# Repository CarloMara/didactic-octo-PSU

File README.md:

# **Didactic PSU**

**An efficient finals project**

So, @nicogela and I decided to build a LAB PSU, but because we're lazy people and we don't like to carry weight we're tring to unite the high efficiency of the switching topologies to the high stability and low noise of the linear ones.

Up until now we've designed the linear stage, and we added to it some DACs in oreder to controll it with a uC. The next stage in the design process will be the testing of the linear + the dacs. If everithing works we will go ahead adding to the desing the switching stage.

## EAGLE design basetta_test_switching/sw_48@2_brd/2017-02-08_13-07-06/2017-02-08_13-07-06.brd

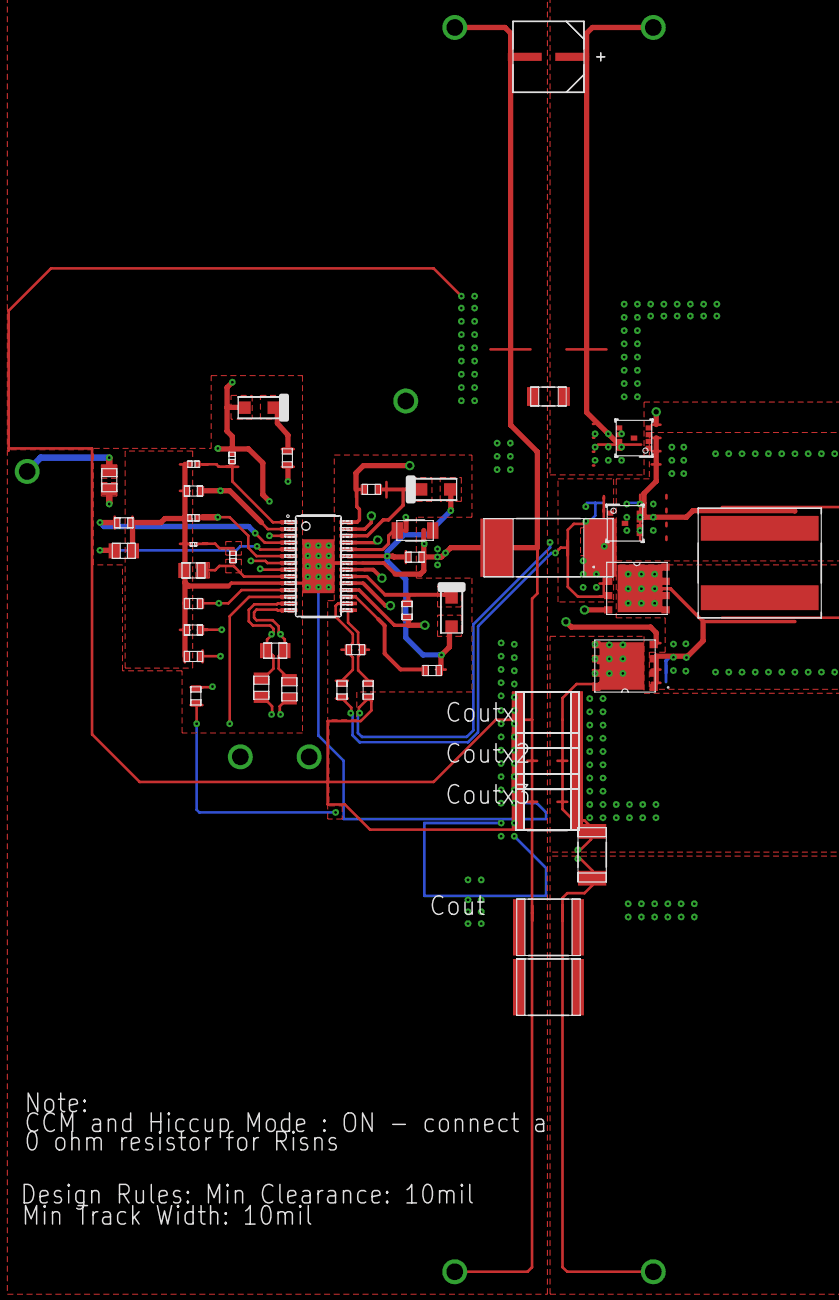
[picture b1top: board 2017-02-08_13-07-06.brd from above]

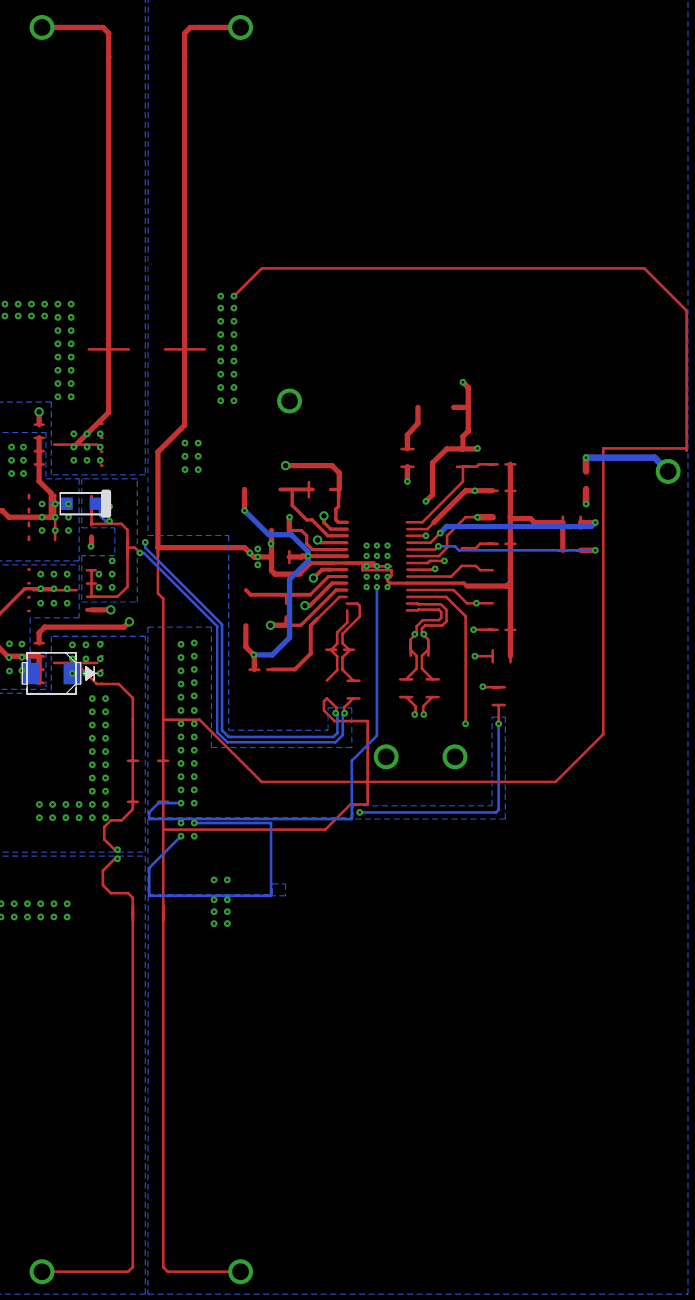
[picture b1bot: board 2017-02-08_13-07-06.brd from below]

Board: 4 copper layers, 66 parts (2 on the bottom side), 27 nets.

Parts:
Cbias: 1206
Cboot1, Cboot2: 0603
Cbulk: SM_RADIAL_6.3AMM
Ccomp: 0201
Ccomp2: 0805
Ccs: 0603
Cdith: 0805
Cf: 0603
Cin: 1206_190
Cisns: 0805
Cout_1, Cout_2: 2220_280
Coutx2_1, Coutx2_2, Coutx2_3, Coutx2_4, Coutx2_5, Coutx3_1, Coutx3_2, Coutx3_3, Coutx3_4, Coutx3_5: 2220
Coutx_1, Coutx_2, Coutx_3, Coutx_4, Coutx_5: 2220
Cslope: 0603
Css: 0603
Csync: 0805
Cvcc: 0603
D2: SOD-123F
D3: SMB
Dboot1, Dboot2: SOD-123F
Df: SOD-123F
GND, GND1: TP-1502
INSNS+: TP-1502
INSNS-: TP-1502
L1: XAL1010
M1, M2: DQG0008A
M3, M4: TRANS_NexFET_Q5A
Rcomp: 0402
Rcsg: 0603
Rcsp: 0603
Rf: 0603
Rfbb: 0603
Rfbt: 0603
Risns: 2512
Risnsn: 0805
Risnsp: 0805
Rmode: 0603
Rpg: 0603
Rsense: 4527
Rt: 0402
Ruvb: 0402
Ruvt: 0402
U1: PWP0028F_N
V1: TP-1502
VIN: TP-1502
VOUT: TP-1502
Vsync: TP-1502

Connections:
0: Cbias.2, Cbulk.2, Ccomp.2, Ccomp2.2, Cdith.1, Cdith.2, Cf.2, Cin.2, Cisns.1, Cisns.2, Cout_1.2, Cout_2.2, Coutx2_1.2, Coutx2_2.2, Coutx2_3.2, Coutx2_4.2, Coutx2_5.2, Coutx3_1.2, Coutx3_2.2, Coutx3_3.2, Coutx3_4.2, Coutx3_5.2, Coutx_1.2, Coutx_2.2, Coutx_3.2, Coutx_4.2, Coutx_5.2, Cslope.2, Css.2, Cvcc.2, GND.1, GND1.1, INSNS+.1, INSNS-.1, Rcsg.2, Rfbb.2, Risnsn.1, Risnsp.1, Rmode.2, Rsense.2, Rt.2, Ruvb.2, U1.5, U1.10, U1.13, U1.14, U1.22, U1.29
1: Css.1, U1.8
2: Rmode.1, U1.4
3: Cbulk.1, Cin.1, Df.2, M1.5, M1.6, M1.7, M1.8, M1.9, Ruvt.1, U1.3, VIN.1
4: Ccomp2.1, Rcomp.1, U1.9
5: Ruvb.1, Ruvt.2, U1.1
6: Csync.1, Rt.1, U1.6
7: D2.2, M2.1, M2.2, M2.3, M4.1, M4.2, M4.3, Rcsp.2, Rsense.1
8: Cslope.1, U1.7
9: Cf.1, Rf.2, U1.2
10: Ccs.1, Rcsp.1, U1.16
11: Ccs.2, Rcsg.1, U1.15
15: Rpg.2, U1.17
16: Rfbb.1, Rfbt.2, U1.11
18: Cboot1.1, Dboot1.1, U1.26
19: Cbias.1, Cout_1.1, Cout_2.1, Coutx2_1.1, Coutx2_2.1, Coutx2_3.1, Coutx2_4.1, Coutx2_5.1, Coutx3_1.1, Coutx3_2.1, Coutx3_3.1, Coutx3_4.1, Coutx3_5.1, Coutx_1.1, Coutx_2.1, Coutx_3.1, Coutx_4.1, Coutx_5.1, D3.1, M3.5, M3.6, M3.7, M3.8, M3.9, Rfbt.1, Risns.1, Risns.2, Risnsn.2, Risnsp.2, U1.12, U1.24, V1.1, VOUT.1
20: Cboot2.2, D3.2, L1.2, M3.1, M3.2, M3.3, M4.5, M4.6, M4.7, M4.8, M4.9, U1.18
21: Cvcc.1, Dboot1.2, Dboot2.2, Rpg.1, U1.23
22: Cboot1.2, D2.1, L1.1, M1.1, M1.2, M1.3, M2.5, M2.6, M2.7, M2.8, M2.9, U1.28
23: Cboot2.1, Dboot2.1, U1.20
24: Ccomp.1, Rcomp.2
25: Df.1, Rf.1
30: M2.4, U1.25
31: M1.4, U1.27
32: M3.4, U1.19
33: M4.4, U1.21
67: Csync.2, Vsync.1

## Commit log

2016-12-24 First Commit, first version of linear stage
2016-12-25 bleeding edge stuff
2016-12-25 README.md edited online with Bitbucket
2016-12-25 changing path to readme
2016-12-25 changing readme
2016-12-26 Updating schematics to reflect the dautherboard desing approch. The uC + DAC schematics has been removed. The dac reference has also been removed. in ordert to switch between pic or manual mode two j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
2016-12-31 Creata cartella con tutti i firmware. Creato esempio uart con mcc. trovato un bacco, ma aspetto che @gela lo riproduca su Windows.
2017-01-02 renamed lineare folder to reflect it's content
2017-01-02 removed lineare folder
2017-01-03 modification on uart example
2017-01-04 Updating PCB routing
2017-01-04 Created spreadsheet to understand in detail the DAC register
2017-01-06 Updating PCB routing and adding PCB edge
2017-01-06 Added a spreadsheet to explaint the varius DAC commands. The spreadsheet can also craft the command in the format used by the bus pirate. Created a project to test the MCC generated libraries. So far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
2017-01-06 Proceding with upgrading @Gela routing
2017-01-06 Same as before
2017-01-06 Splitted one of the daughterboard connector to allow a better routing
2017-01-07 Created the reference of the i2c implementation on mplab. This project it's now fully working, just swap the walues in the array.
2017-01-07 Created a test project that implements all of the PSU core function. Configured the MCC code with all of the peripherics (ADC, I2C, UART). Started to implement serial protocol. See future commit for 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
2017-01-09 Finished PCB "Parte lineare" routing
2017-01-09 added a firmware project for all of the functions modified pcb in order to make it with the matireals avaible
2017-01-12 Updated BOM list and components value
2017-01-27 changed some of the boarda. Added the file of the stm32 nucleo board.
2017-01-30 reorganized the simulation folder, added the switching tracking simulation
2017-02-01 Addin DC/DC boost-buck eeschema
2017-02-09 reorganized switching folder
2017-02-09 Added switching controller bom
2017-02-13 Adding schematic of boost/buck switching stage
2017-02-13 It say"commit"
2017-02-16 Finished footprints association -> ready for PCB routing!
2017-02-20 Added libraries, hopefully
2017-02-20 Ready for BOM
2017-02-20 Adding official TI PDF so @CarloMara is happy;
2017-02-23 Updated EESCHEMA , full footprin association and started PCB
2017-02-27 PCB update
2017-03-05 Reorganized Folder Structure
2017-03-05 Remove unnecessary files
2017-03-05 Progress on the routng of the H-Bridge
2017-03-06 Updated routing
2017-03-06 Moved resistor
2017-03-06 PCB of SW48A2
    Need more footprint for wire pad for single layer routing... need revision
2017-03-07 Updating PCB routing of sw48
2017-03-07 Finished PCB routing of SW48A2->ready for revision and prototyping
2017-03-09 More routing
2017-03-09 Routing and routing....
2017-03-13 Revised the linear part to adapt to the results of preliminary tests
2017-03-14 SW48A2 routing..
2017-03-23 Update of Sw48A2
2017-04-06 New board that include NUCLEO F303K8
2017-04-07 Adding lineare files
2017-04-07 work dir reorganized
2017-04-07 adedd kicad gitignore
2017-04-10 adedd front panel documents
    In the documents folder it's provided a pdf with the schematics of the bard with the display and the graphic display, and the encoder.
2017-04-11 New pcb about NUCLEO(ARM) and DAC for linear PSU regulation
2017-04-12 reviewed the schematics made by gela
    1-sistemare il bus
    2-finire la resistenza di biasing del reference
    3-mettere degli amplificatori per disaccopiare i dac
    4-predisporre per gli ingressi degli adc
    5-capire come gesire le alimentazioni ci penso io
2017-04-12 Adding annotation on kicad sheet
2017-04-17 Update..
2017-04-18 drawn a better schematic
    This new schemati reflects better the function of eatch passives and also uses less labes
2017-04-19 Labels on schematics, annotation and component assocation
    done
2017-04-19 Started Routing
    Changed pad assocation on the lm5175 footprint. Layed out the power components, in an efficient layout for shilding
2017-04-19 New netlist with lm5175 updated footprint
2017-04-19 Progress in routing
    Routed some of the passives
2017-04-20 Finished routing
2017-04-20 Deleting DAC and Reference
    Ciao Carlo!
2017-04-23 Shorted some wires for better performance
2017-04-24 Proceding with routing on Nucleo board
2017-04-24 Finish routing of basetta..
    Carlo must find something wrong...
2017-04-30 Progress on lineare rev3
    Created the kicad project and some of the libs!
2017-05-01 Progress on schematics
    DONE:
    -I2C insulation
    -DAC connection
    -DAC signal contitioning
    -Error amplifiers(both for voltage & current)
    -Pass element + gate control
2017-05-01 Removed useless libraries from project file
2017-05-01 Added linear regulators
2017-05-01 Picking footprints
2017-05-01 Revised work done by @NikoGela
    A few things have changed, to make it more clear schematic and routing changes are separated.
    #Schematic
    -removed the led that was used to show if the regulator was working
    -removed the power traces from the signal bus
    -broken out the connection for the I2C. see routing for futher details
    -changed the eletrolitic caps from THT to SMD
2017-05-03 Added mounting holes
2017-05-03 Relayed board to fit mounting holes
2017-05-04 Added docs
2017-05-04 Add special library for special components...
    Like dc dc converter,opamp etc..
2017-05-05 Created project for pd board
2017-05-05 Created footprint for dcdc converter
2017-05-05 New design for power distribution
2017-05-05 Flipped board to adjust for final board stack
2017-05-05 Final revision of schematic
    -added pullup resistor on i2c from digital side
    -added reference using lm4040. Our ic is the 2.5V version
    -checked the signal conditioning stage to get it working with changed reference
    WHEN TESTING IS POSSIBLE THAT THERE WILL BE SOME PROBLEMS WITH THE DAC & THE REFERENCE. The proposed solution is to cut the traces to the reference, use VDD as a reference and change the signal condi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
2017-05-05 Removed 75xx regulator from linear board
    In order to save space thoose components have been moved to the pd board
2017-05-05 Routed power delivery and linear reguletors
2017-05-05 Routed pd and regulators
2017-05-05 Added ground planes
2017-05-05 Created solid ground planes
    Cause thermal relief is for kids
2017-05-07 Added mountig holes and checked drc
2017-05-07 Added groundplanes and done DRC
2017-05-07 Added ground planes, moved I2C connector
    The I2C connector was moved to accomodate the changes done in the lineare board
2017-05-08 Swapped for LDO, ground planes
2017-05-08 Done things in power distribution
2017-05-08 Other major modification
2017-05-08 Adding hole for I2C bus in logic_power_distribution board
2017-05-08 Finished revising basetta_power_distribution
2017-05-08 Last change for power_distribution..
2017-05-08 Added labels
2017-05-08 NOW IT?S COMPLETE!
2017-05-22 Removed ground planes
    You can't see shit if they are off
